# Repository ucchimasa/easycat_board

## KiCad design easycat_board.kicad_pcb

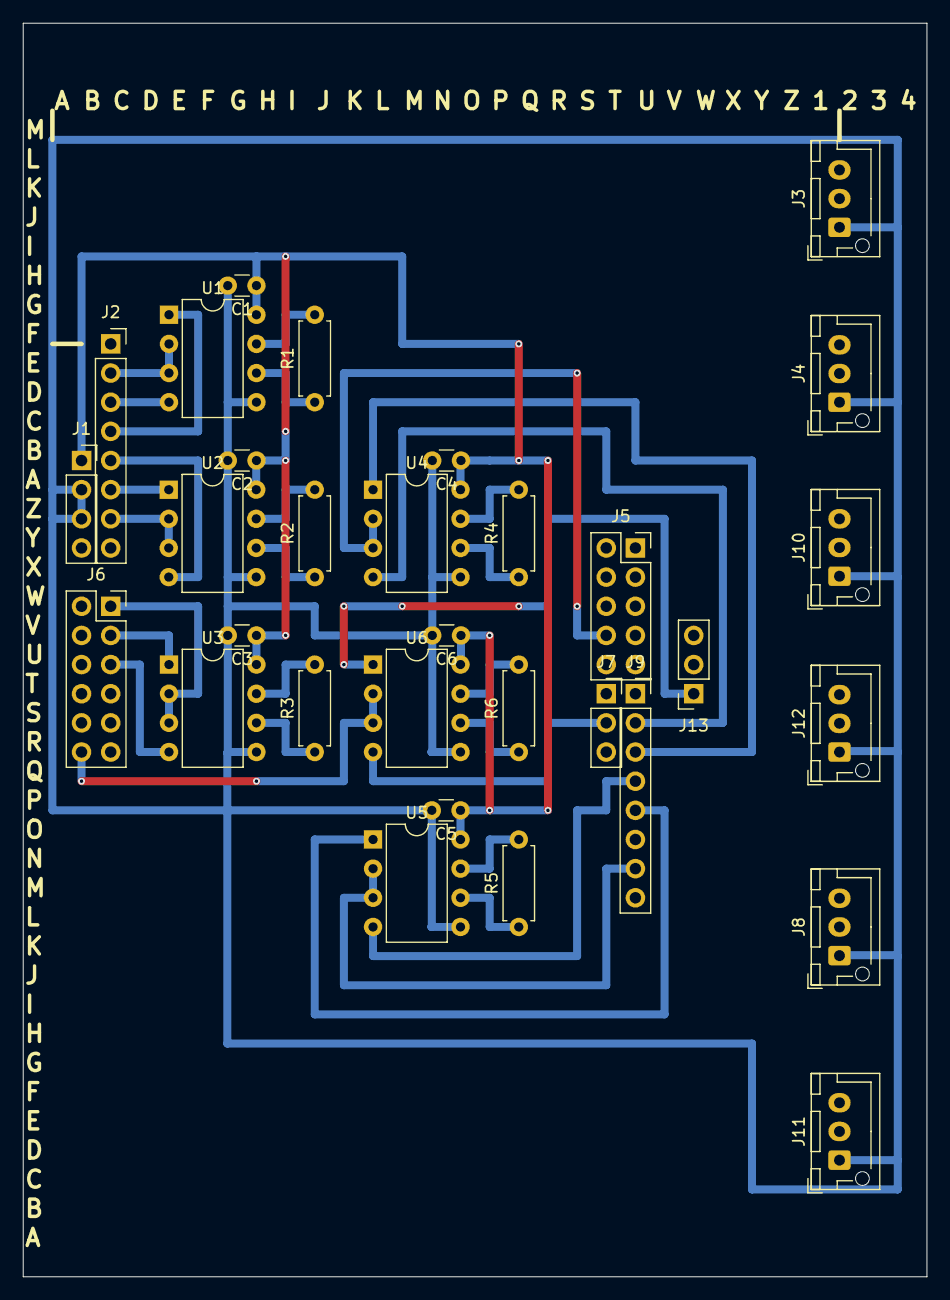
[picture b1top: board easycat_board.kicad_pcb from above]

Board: 4 copper layers, 78.7 x 109.2 mm, 31 parts (0 on the bottom side), 24 nets.

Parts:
C1, C2, C3, C4, C5, C6: 0.1u; C_Disc_D3.0mm_W1.6mm_P2.50mm
J1: Conn_01x04_Pin; PinSocket_1x04_P2.54mm_Vertical
J2, J9: Conn_01x08_Pin; PinSocket_1x08_P2.54mm_Vertical
J3, J4, J8, J10, J11, J12: Conn_01x03_Pin; JST_XH_B3B-XH-AM_1x03_P2.50mm_Vertical
J5: Conn_02x05_Odd_Even; PinSocket_2x05_P2.54mm_Vertical
J6: Conn_02x06_Odd_Even; PinSocket_2x06_P2.54mm_Vertical
J7, J13: Conn_01x03_Pin; PinSocket_1x03_P2.54mm_Vertical
R1, R2, R3, R4, R5, R6: 120; R_Axial_DIN0207_L6.3mm_D2.5mm_P7.62mm_Horizontal
U1, U2, U3, U4, U5, U6: MAX485E; DIP-8_W7.62mm

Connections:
+5V: C1.1, C1.2, C2.1, C2.2, C3.1, C3.2, C4.1, C4.2, C5.1, C5.2, C6.1, C6.2, J1.1, J1.2, J1.3, J3.1, J4.1, J4.2, J4.3, J5.8, J6.12, J8.1, J8.2, J8.3, J9.5, J10.1, J11.1, J12.1, R2.1, R2.2, R3.1, R3.2, U1.5 (GND), U1.8 (VCC), U2.5 (GND), U2.6 (A), U2.7 (B), U2.8 (VCC), U3.5 (GND), U3.6 (A), U3.7 (B), U3.8 (VCC), U4.2 (~RE), U4.3 (DE), U4.5 (GND), U4.8 (VCC), U5.1 (RO), U5.5 (GND), U5.8 (VCC), U6.2 (~RE), U6.3 (DE), U6.5 (GND), U6.8 (VCC)
/A_1: J3.2, R1.1, U1.6 (A)
/A_4: J10.2, R4.1, U4.6 (A)
/A_5: J11.2, R5.1, U5.6 (A)
/A_6: J12.2, R6.1, U6.6 (A)
/B_1: J3.3, R1.2, U1.7 (B)
/B_4: J10.3, R4.2, U4.7 (B)
/B_5: J11.3, R5.2, U5.7 (B)
/B_6: J12.3, R6.2, U6.7 (B)
/EN_2: J6.1, U3.2 (~RE), U3.3 (DE)
/EN_4: J2.2, U1.2 (~RE), U1.3 (DE)
/EN_5: J2.7, U2.2 (~RE), U2.3 (DE)
/EN_7: J9.7, U5.2 (~RE), U5.3 (DE)
/UART1_RX: J13.1, U6.1 (RO)
/UART1_TX: J7.2, U6.4 (DI)
/UART2_RX: J6.3, U3.1 (RO)
/UART2_TX: J6.5, U3.4 (DI)
/UART4_RX: J2.4, U1.1 (RO)
/UART4_TX: J2.3, U1.4 (DI)
/UART5_RX: J2.6, U2.1 (RO)
/UART5_TX: J2.5, U2.4 (DI)
/UART6_RX: J9.3, U4.1 (RO)
/UART6_TX: J9.2, U4.4 (DI)
/UART7_TX: J9.4, U5.4 (DI)

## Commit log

2025-03-27 6つポート搭載のシールド基板
